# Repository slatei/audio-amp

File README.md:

View this project on [CADLAB.io](https://cadlab.io/project/1181). 

# audio-amp

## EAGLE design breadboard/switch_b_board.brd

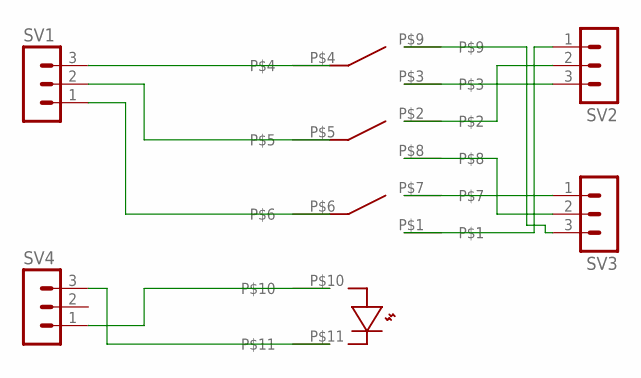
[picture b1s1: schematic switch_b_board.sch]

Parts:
SV1, SV2, SV3, SV4: MA03-1
U$1: FOOT_SWITCH

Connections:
unnamed: SV1.1, U$1.P$6
unnamed: SV1.2, U$1.P$5
unnamed: SV1.3, U$1.P$4
unnamed: SV2.1, U$1.P$1
unnamed: SV2.3, U$1.P$3
unnamed: SV2.2, U$1.P$2
unnamed: SV3.3, U$1.P$9
unnamed: SV3.1, U$1.P$7
unnamed: SV3.2, U$1.P$8
unnamed: SV4.1, U$1.P$10
unnamed: SV4.3, U$1.P$11

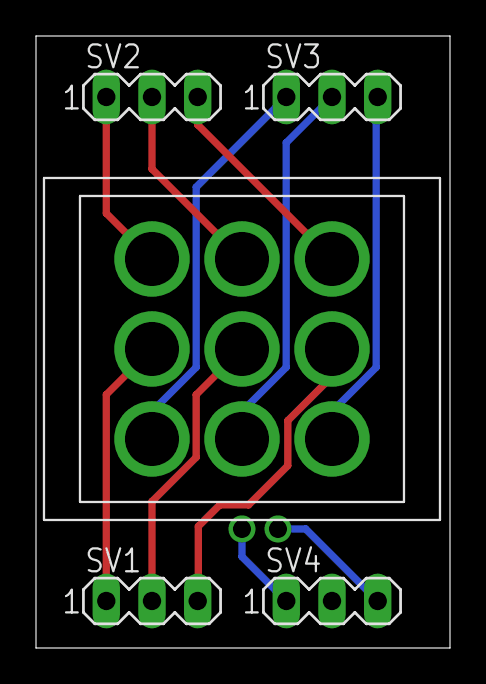
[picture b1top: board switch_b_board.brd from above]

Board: 2 copper layers, 23.0 x 34.0 mm, 5 parts (0 on the bottom side), 11 nets.

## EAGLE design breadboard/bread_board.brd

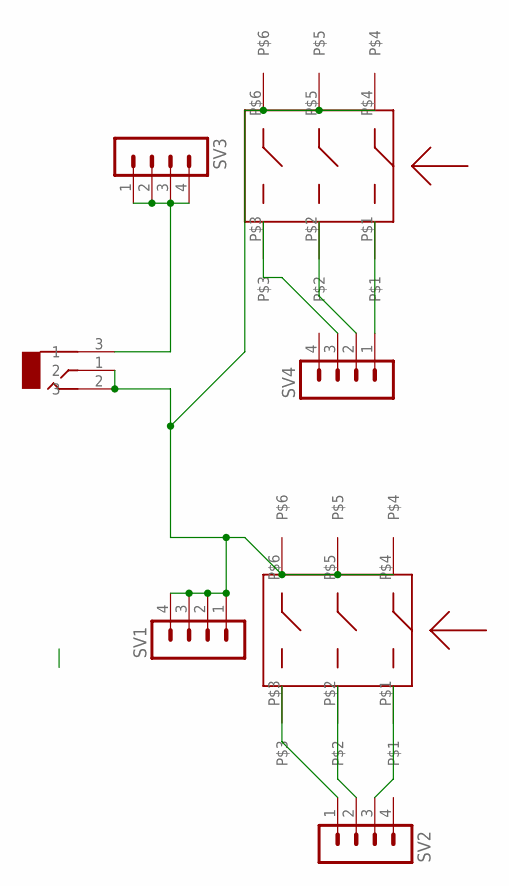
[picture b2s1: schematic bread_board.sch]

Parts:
J2: DC_JACK
SV1, SV2, SV3, SV4: MA04-1
U$1, U$2: AUDIO_JACK

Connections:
GND: J2.1 (2), J2.2 (3), SV1.1, SV1.2, SV1.3, SV1.4, U$1.P$4, U$1.P$5, U$1.P$6, U$2.P$4, U$2.P$5, U$2.P$6
unnamed: SV2.3, U$2.P$1
unnamed: J2.3 (1), SV3.1, SV3.2, SV3.3, SV3.4
unnamed: SV2.2, U$2.P$2
unnamed: SV2.1, U$2.P$3
unnamed: SV4.1, U$1.P$1
unnamed: SV4.2, U$1.P$2
unnamed: SV4.3, U$1.P$3

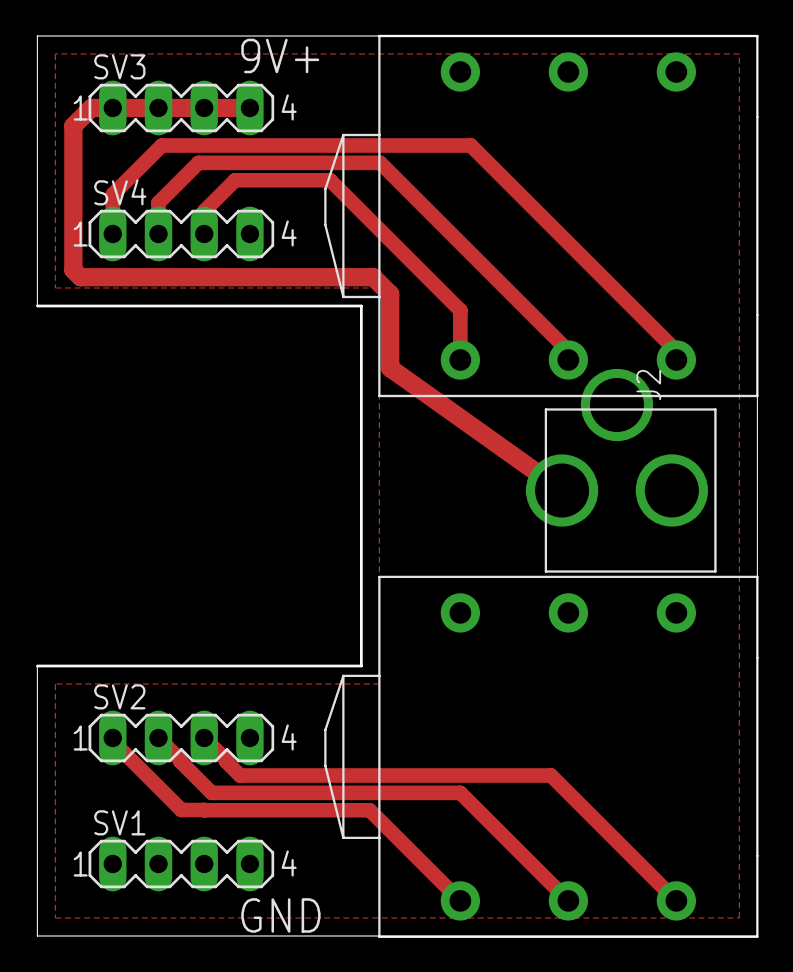
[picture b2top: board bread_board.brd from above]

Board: 2 copper layers, 40.0 x 50.0 mm, 7 parts (0 on the bottom side), 8 nets.

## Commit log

2018-06-19 added PCB schematic files
2018-06-19 Backlink to CADLAB.io has been added.
2018-06-19 Straightened up the lines and added text
2018-06-19 Added breadboard for viewing
2018-06-19 Updated or downgraded bread board
